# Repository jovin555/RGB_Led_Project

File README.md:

# ESP32 WS2812B LED Controller

A simple RGB LED chain controller for lighting up a Christmas tree with an ESP32. It is a 4-output, 5 V addressable LED controller built around the ESP32-S3-WROOM-1, designed to run [WLED](https://kno.wled.ge/). The repo holds the KiCad design, a 3D-printable enclosure, and the build and programming docs.

## Features

- **ESP32-S3-WROOM-1** (N8 or N8R8) with Wi-Fi, flashed over native USB-C. No USB-UART chip needed.
- **4 LED outputs** (GPIO4–7) through a 74AHCT125 3.3 V → 5 V level shifter, each on a 3-pin terminal (+5V / DATA / GND).
- **5 V input up to 10 A** through a screw terminal, plus a barrel jack (≤5 A), protected by a 7.5 A blade fuse and an SMBJ5.0A TVS diode.
- USB-C powers the logic for programming, isolated from the LED supply by ORing diodes and a 500 mA PTC.
- RST and BOOT buttons, a backup UART header (J3), and test points on every power rail.
- 110 × 85 mm, 2-layer board with 2 oz copper, laid out for JLCPCB assembly. ERC and DRC are clean (rev 0.2).

## Repository layout

| Path | Contents |
| --- | --- |
| [kicad/](kicad/) | KiCad project: schematic (root plus power, MCU, USB and LED-output sheets), PCB and project library |
| [enclosure/](enclosure/) | Parametric enclosure (CadQuery), printable STL/STEP parts, full assembly STEP and renders |
| [firmware/docs/](firmware/docs/) | Programming guide for WLED and Arduino/PlatformIO |
| [docs/](docs/) | Design plan, layout notes, enclosure design and images (each as Markdown and PDF) |
| [tools/kigen/](tools/kigen/) | Python scripts that generate the schematic sheets and PCB |

## Documentation

- [PCB design plan](docs/PCB_DESIGN_PLAN.md): why an ESP32, requirements, schematic blocks and BOM
- [Schematic and layout notes](docs/PCB_LAYOUT_NOTES.md): rev 0.2 status, changes, review fixes and the pre-order checklist
- [Enclosure design](docs/ENCLOSURE_DESIGN.md): how to view, print, order and assemble the enclosure
- [Programming guide](firmware/docs/PROGRAMMING_GUIDE.md): flashing WLED or your own code, pin map and troubleshooting

## Quick start

1. **Build the board:** open `kicad/esp32_led_controller.kicad_pro` in KiCad, then export Gerbers, BOM and positions for ordering. See [Check before ordering](docs/PCB_LAYOUT_NOTES.md#check-before-ordering).
2. **Print the enclosure:** print `enclosure/enclosure_base.stl`, `enclosure/enclosure_lid.stl` and two `enclosure/button_plunger.stl`. You'll also need four M3 screws and heat-set inserts ([parts list](docs/ENCLOSURE_DESIGN.md#parts-to-buy)).
3. **Flash WLED:** connect USB-C and use the WLED web installer ([guide](firmware/docs/PROGRAMMING_GUIDE.md#option-a-wled-recommended)). Set the LED outputs to GPIO 4, 5, 6 and 7.

## Regenerating

From the project root:

```bash
python3 -I tools/kigen/design.py     # rewrite the four schematic sub-sheets
# Do not run tools/kigen/pcbgen.py: it rebuilds the board and discards all routing.
python3 enclosure/enclosure.py       # rebuild the enclosure STL/STEP parts
python3 enclosure/make_assembly.py   # rebuild the assembly STEP files
```

Before you run these, read the Regenerating sections in [PCB_LAYOUT_NOTES.md](docs/PCB_LAYOUT_NOTES.md#regenerating) and [ENCLOSURE_DESIGN.md](docs/ENCLOSURE_DESIGN.md#regenerating) for the dependencies and caveats.

## Status

Rev 0.2: the design is complete and the board has not been fabricated yet.

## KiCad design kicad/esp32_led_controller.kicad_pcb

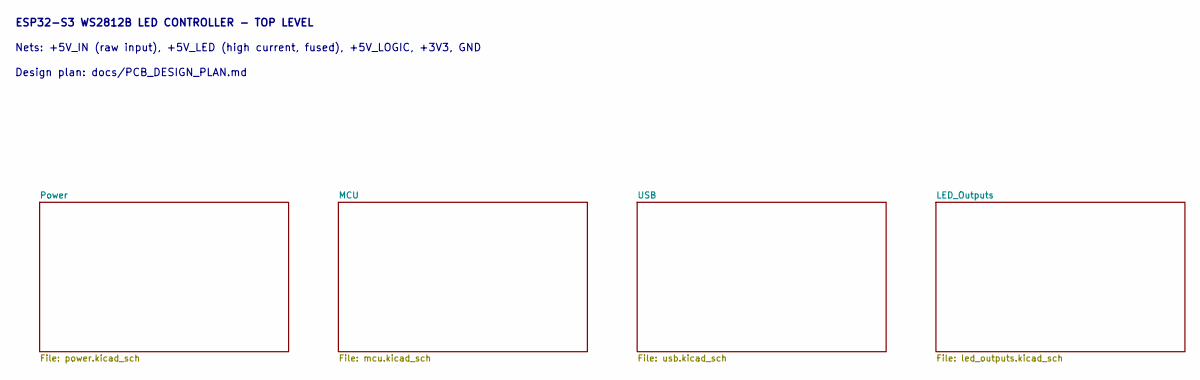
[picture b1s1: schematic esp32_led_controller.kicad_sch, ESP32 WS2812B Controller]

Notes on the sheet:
Design plan: docs/PCB_DESIGN_PLAN.md
ESP32-S3 WS2812B LED CONTROLLER - TOP LEVEL
Nets: +5V_IN (raw input), +5V_LED (high current, fused), +5V_LOGIC, +3V3, GND

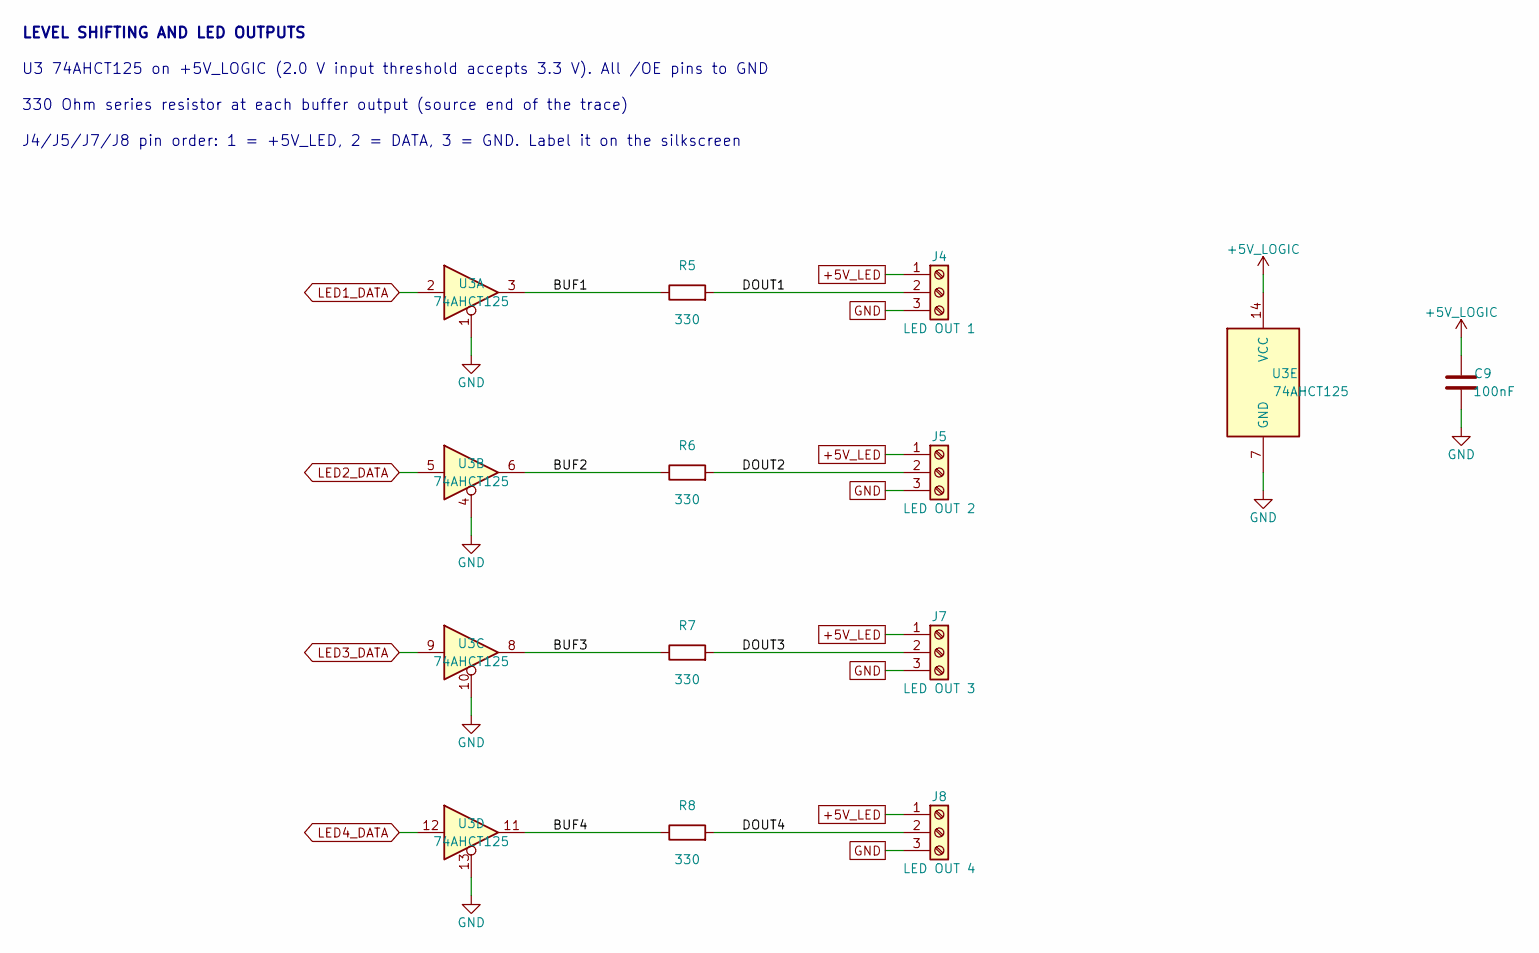
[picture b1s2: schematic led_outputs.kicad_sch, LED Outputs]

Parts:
C9: 100nF; C_0603_1608Metric
J4: LED OUT 1; TerminalBlock_Phoenix_MKDS-1,5-3-5.08_1x03_P5.08mm_Horizont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
J5: LED OUT 2; TerminalBlock_Phoenix_MKDS-1,5-3-5.08_1x03_P5.08mm_Horizont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
J7: LED OUT 3; TerminalBlock_Phoenix_MKDS-1,5-3-5.08_1x03_P5.08mm_Horizont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
J8: LED OUT 4; TerminalBlock_Phoenix_MKDS-1,5-3-5.08_1x03_P5.08mm_Horizont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
R5, R6, R7, R8: 330; R_0603_1608Metric
U3: 74AHCT125; SOIC-14_3.9x8.7mm_P1.27mm

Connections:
+5V_LED: J4.1, J5.1, J7.1, J8.1; also elsewhere on the board
+5V_LOGIC: C9.1, U3.14 (VCC); also elsewhere on the board
/LED_Outputs/BUF1: R5.1, U3.3
/LED_Outputs/BUF2: R6.1, U3.6
/LED_Outputs/BUF3: R7.1, U3.8
/LED_Outputs/BUF4: R8.1, U3.11
/LED_Outputs/DOUT1: J4.2, R5.2
/LED_Outputs/DOUT2: J5.2, R6.2
/LED_Outputs/DOUT3: J7.2, R7.2
/LED_Outputs/DOUT4: J8.2, R8.2
GND: C9.2, J4.3, J5.3, J7.3, J8.3, U3.1, U3.4, U3.7 (GND), U3.10, U3.13; also elsewhere on the board
LED1_DATA: U3.2; also elsewhere on the board
LED2_DATA: U3.5; also elsewhere on the board
LED3_DATA: U3.9; also elsewhere on the board
LED4_DATA: U3.12; also elsewhere on the board

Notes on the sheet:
LEVEL SHIFTING AND LED OUTPUTS
U3 74AHCT125 on +5V_LOGIC (2.0 V input threshold accepts 3.3 V). All /OE pins to GND
330 Ohm series resistor at each buffer output (source end of the trace)
J4/J5/J7/J8 pin order: 1 = +5V_LED, 2 = DATA, 3 = GND. Label it on the silkscreen

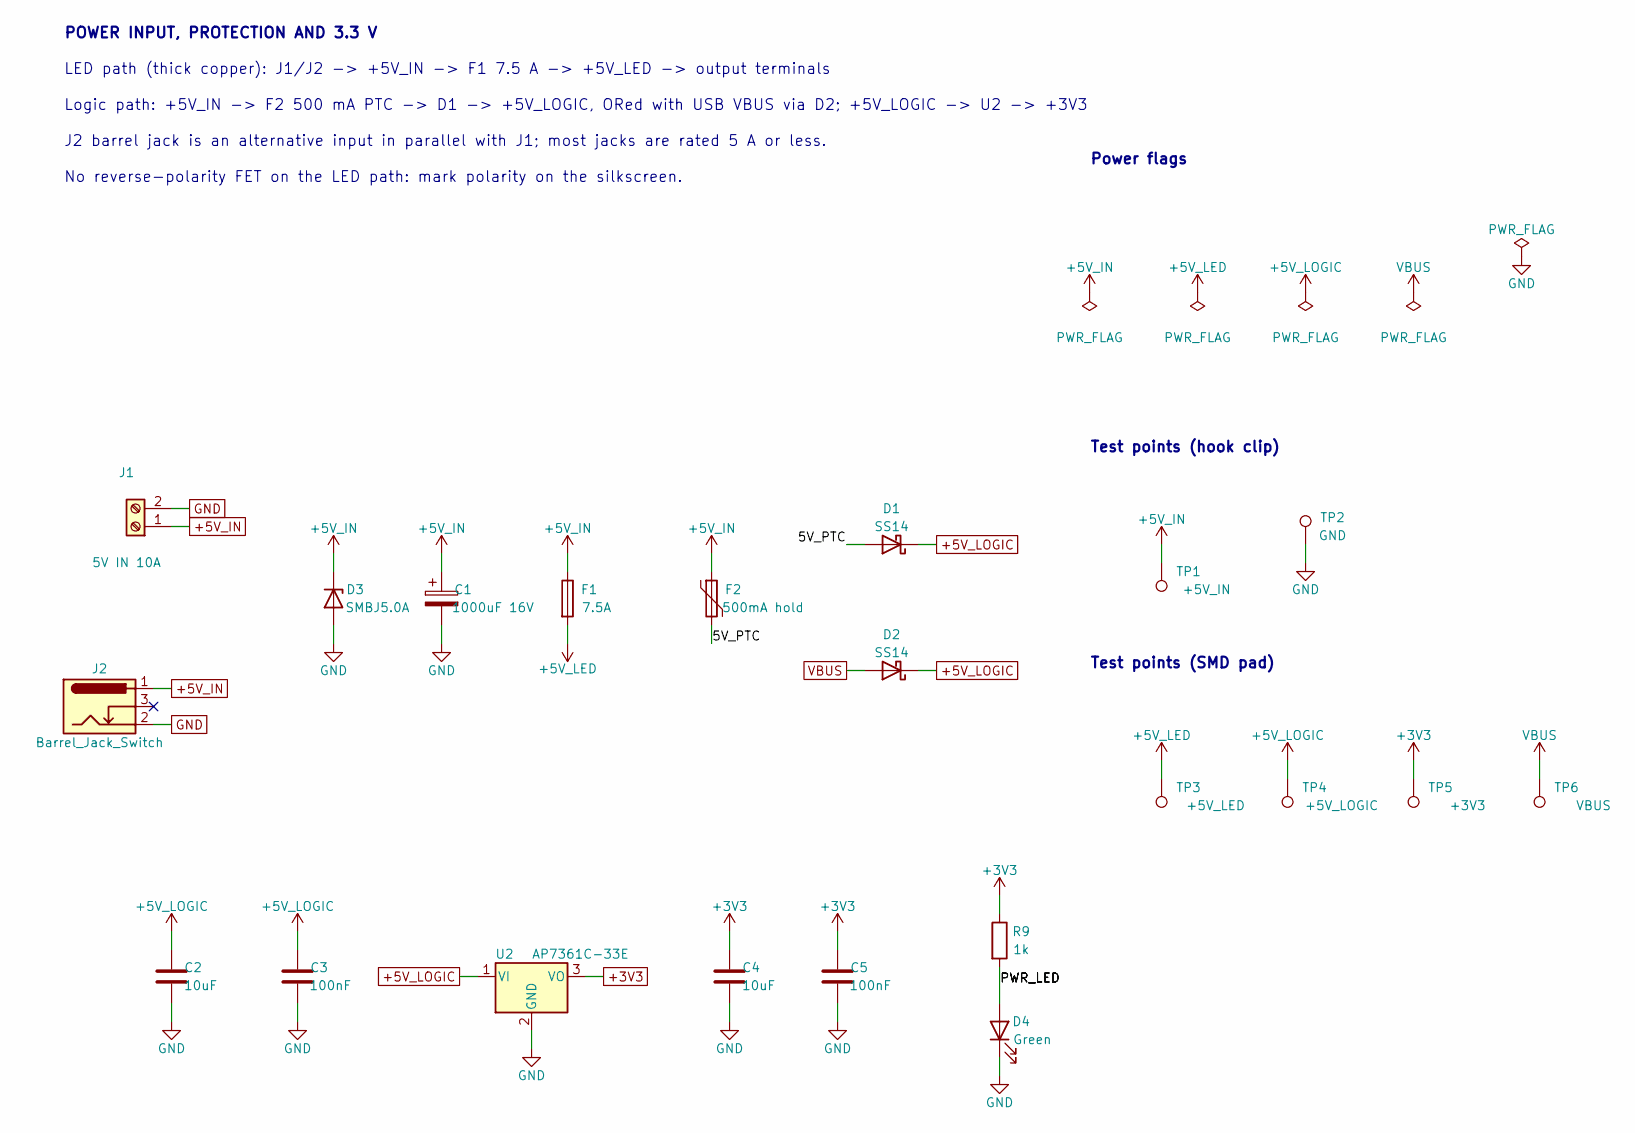
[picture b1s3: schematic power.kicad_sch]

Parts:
C1: 1000uF 16V; CP_Radial_D10.0mm_P5.00mm
C2, C4: 10uF; C_0805_2012Metric
C3, C5: 100nF; C_0603_1608Metric
D1, D2: SS14; D_SMA
D3: SMBJ5.0A; D_SMB
D4: Green; LED_0603_1608Metric
F1: 7.5A; Fuseholder_Blade_Mini_Keystone_3568
F2: 500mA hold; Fuse_1206_3216Metric
J1: 5V IN 10A; TerminalBlock_Phoenix_MKDS-1,5-2-5.08_1x02_P5.08mm_Horizont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
J2: Barrel_Jack_Switch; BarrelJack_Horizontal
R9: 1k; R_0603_1608Metric
TP1: +5V_IN; TestPoint_Keystone_5005-5009_Compact; MPN Keystone 5005 (red)
TP2: GND; TestPoint_Keystone_5005-5009_Compact; MPN Keystone 5006 (black)
TP3: +5V_LED; TestPoint_Pad_D1.5mm
TP4: +5V_LOGIC; TestPoint_Pad_D1.5mm
TP5: +3V3; TestPoint_Pad_D1.5mm
TP6: VBUS; TestPoint_Pad_D1.5mm
U2: AP7361C-33E; SOT-223-3_TabPin2

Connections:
+3V3: C4.1, C5.1, R9.1, TP5.1, U2.3 (VO); also elsewhere on the board
+5V_IN: C1.1, D3.1 (K), F1.1, F2.1, J1.1, J2.1, TP1.1
+5V_LED: F1.2, TP3.1; also elsewhere on the board
+5V_LOGIC: C2.1, C3.1, D1.1 (K), D2.1 (K), TP4.1, U2.1 (VI); also elsewhere on the board
/Power/5V_PTC: D1.2 (A), F2.2
/Power/PWR_LED: D4.2 (A), R9.2
GND: C1.2, C2.2, C3.2, C4.2, C5.2, D3.2 (A), D4.1 (K), J1.2, J2.2, TP2.1, U2.2 (GND); also elsewhere on the board
VBUS: D2.2 (A), TP6.1; also elsewhere on the board

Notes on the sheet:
POWER INPUT, PROTECTION AND 3.3 V
LED path (thick copper): J1/J2 -> +5V_IN -> F1 7.5 A -> +5V_LED -> output terminals
Logic path: +5V_IN -> F2 500 mA PTC -> D1 -> +5V_LOGIC, ORed with USB VBUS via D2; +5V_LOGIC -> U2 -> +3V3
J2 barrel jack is an alternative input in parallel with J1; most jacks are rated 5 A or less.
No reverse-polarity FET on the LED path: mark polarity on the silkscreen.
Test points (hook clip)
Test points (SMD pad)
Power flags

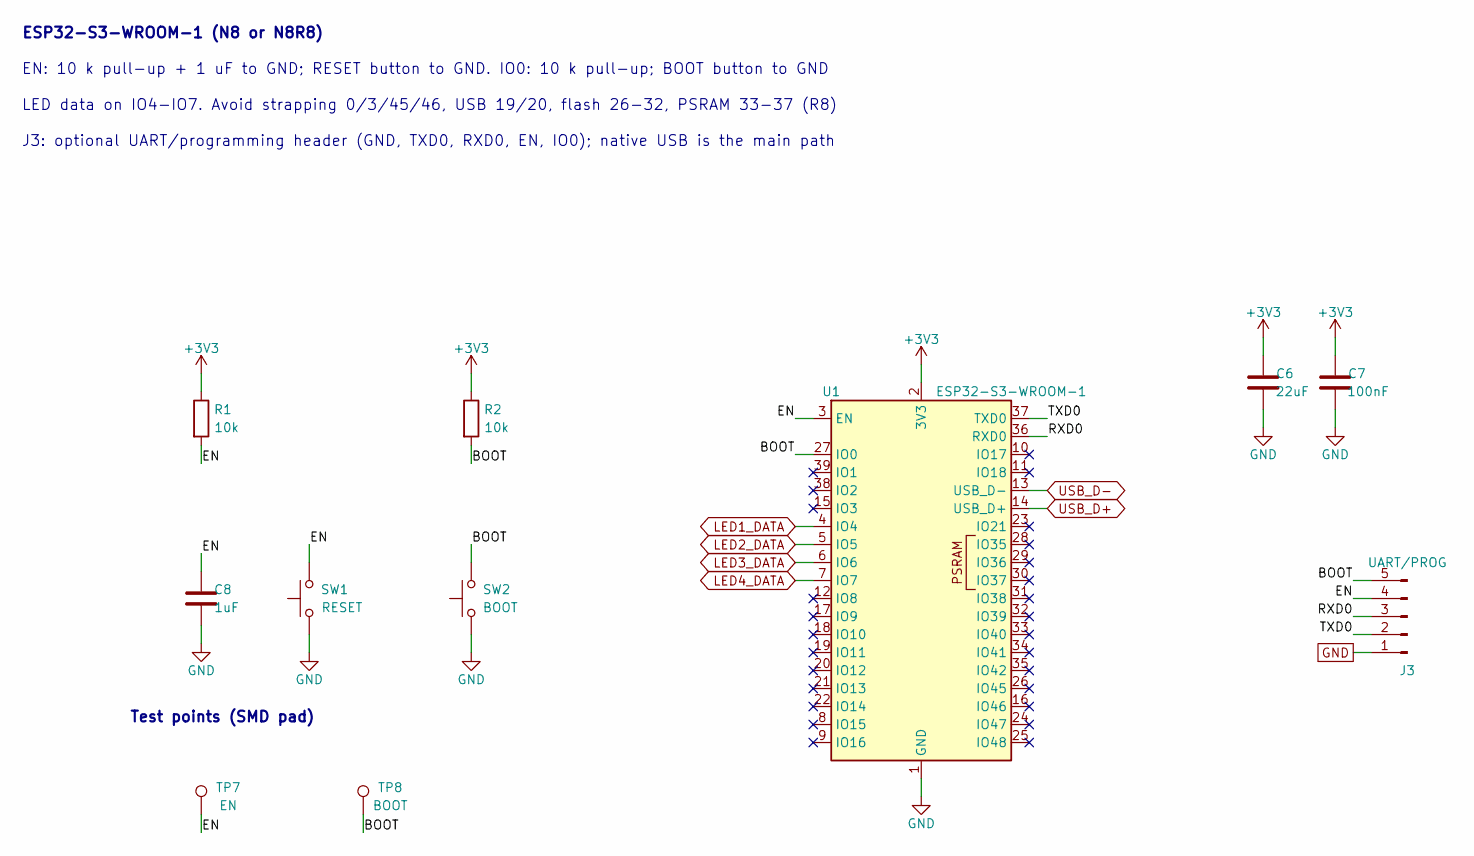
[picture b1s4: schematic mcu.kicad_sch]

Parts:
C6: 22uF; C_0805_2012Metric
C7: 100nF; C_0603_1608Metric
C8: 1uF; C_0603_1608Metric
J3: UART/PROG; PinHeader_1x05_P2.54mm_Vertical
R1, R2: 10k; R_0603_1608Metric
SW1: RESET; SW_SPST_TL3342
SW2: BOOT; SW_SPST_TL3342
TP7: EN; TestPoint_Pad_D1.5mm
TP8: BOOT; TestPoint_Pad_D1.5mm
U1: ESP32-S3-WROOM-1

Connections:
+3V3: C6.1, C7.1, R1.1, R2.1, U1.2 (3V3); also elsewhere on the board
/MCU/BOOT: J3.5, R2.2, SW2.2, TP8.1, U1.27 (IO0)
/MCU/EN: C8.1, J3.4, R1.2, SW1.2, TP7.1, U1.3 (EN)
/MCU/RXD0: J3.3, U1.36 (RXD0)
/MCU/TXD0: J3.2, U1.37 (TXD0)
GND: C6.2, C7.2, C8.2, J3.1, SW1.1, SW2.1, U1.1 (GND), U1.40 (GND), U1.41 (GND); also elsewhere on the board
LED1_DATA: U1.4 (IO4); also elsewhere on the board
LED2_DATA: U1.5 (IO5); also elsewhere on the board
LED3_DATA: U1.6 (IO6); also elsewhere on the board
LED4_DATA: U1.7 (IO7); also elsewhere on the board
USB_D+: U1.14 (USB_D+); also elsewhere on the board
USB_D-: U1.13 (USB_D-); also elsewhere on the board

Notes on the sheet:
ESP32-S3-WROOM-1 (N8 or N8R8)
EN: 10 k pull-up + 1 uF to GND; RESET button to GND. IO0: 10 k pull-up; BOOT button to GND
LED data on IO4-IO7. Avoid strapping 0/3/45/46, USB 19/20, flash 26-32, PSRAM 33-37 (R8)
J3: optional UART/programming header (GND, TXD0, RXD0, EN, IO0); native USB is the main path
Test points (SMD pad)

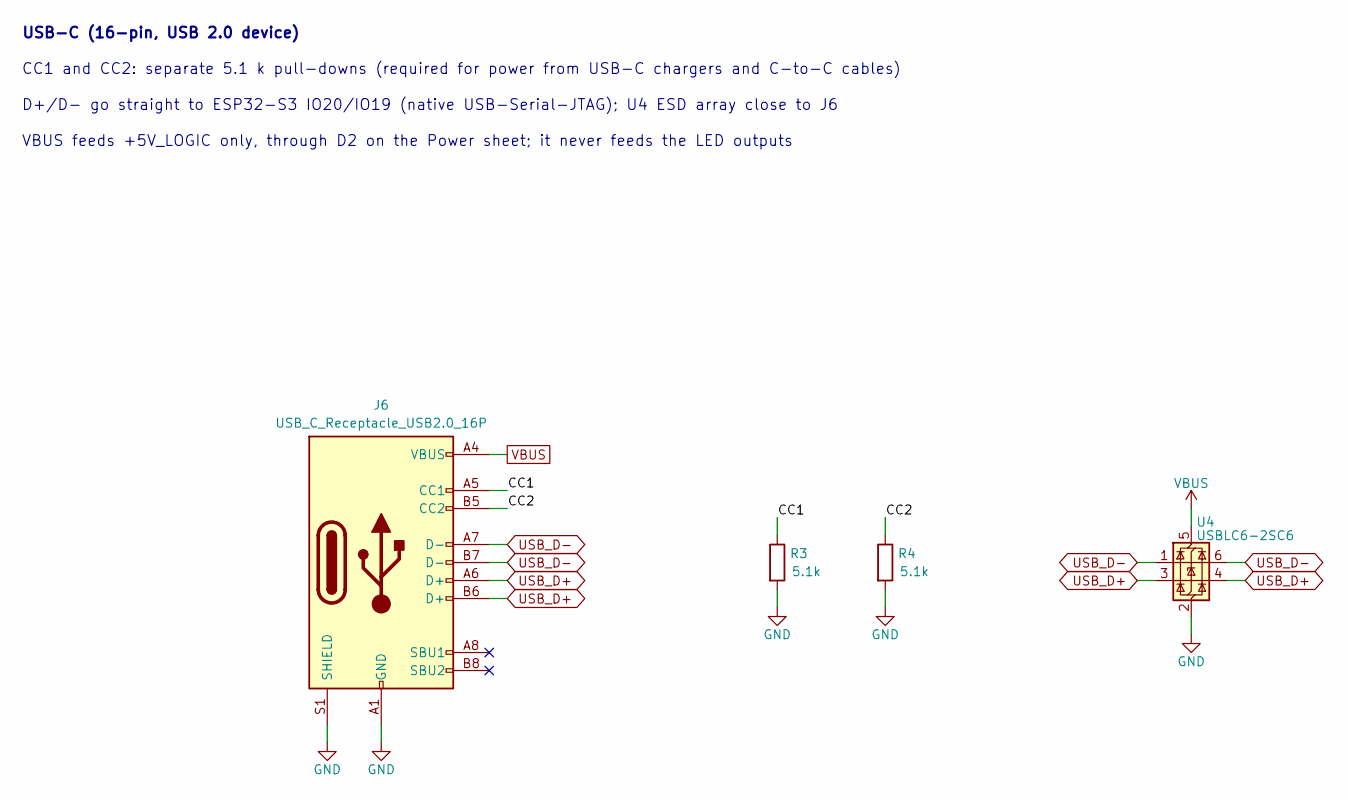
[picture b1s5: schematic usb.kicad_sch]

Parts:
J6: USB_C_Receptacle_USB2.0_16P; USB_C_Receptacle_HRO_TYPE-C-31-M-12
R3, R4: 5.1k; R_0603_1608Metric
U4: USBLC6-2SC6; SOT-23-6

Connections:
/USB/CC1: J6.A5 (CC1), R3.1
/USB/CC2: J6.B5 (CC2), R4.1
GND: J6.A1 (GND), J6.A12 (GND), J6.B1 (GND), J6.B12 (GND), J6.S1 (SHIELD), R3.2, R4.2, U4.2 (GND); also elsewhere on the board
USB_D+: J6.A6 (D+), J6.B6 (D+), U4.3 (I/O2), U4.4 (I/O2); also elsewhere on the board
USB_D-: J6.A7 (D-), J6.B7 (D-), U4.1 (I/O1), U4.6 (I/O1); also elsewhere on the board
VBUS: J6.A4 (VBUS), J6.A9 (VBUS), J6.B4 (VBUS), J6.B9 (VBUS), U4.5 (VBUS); also elsewhere on the board

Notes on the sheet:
USB-C (16-pin, USB 2.0 device)
CC1 and CC2: separate 5.1 k pull-downs (required for power from USB-C chargers and C-to-C cables)
D+/D- go straight to ESP32-S3 IO20/IO19 (native USB-Serial-JTAG); U4 ESD array close to J6
VBUS feeds +5V_LOGIC only, through D2 on the Power sheet; it never feeds the LED outputs

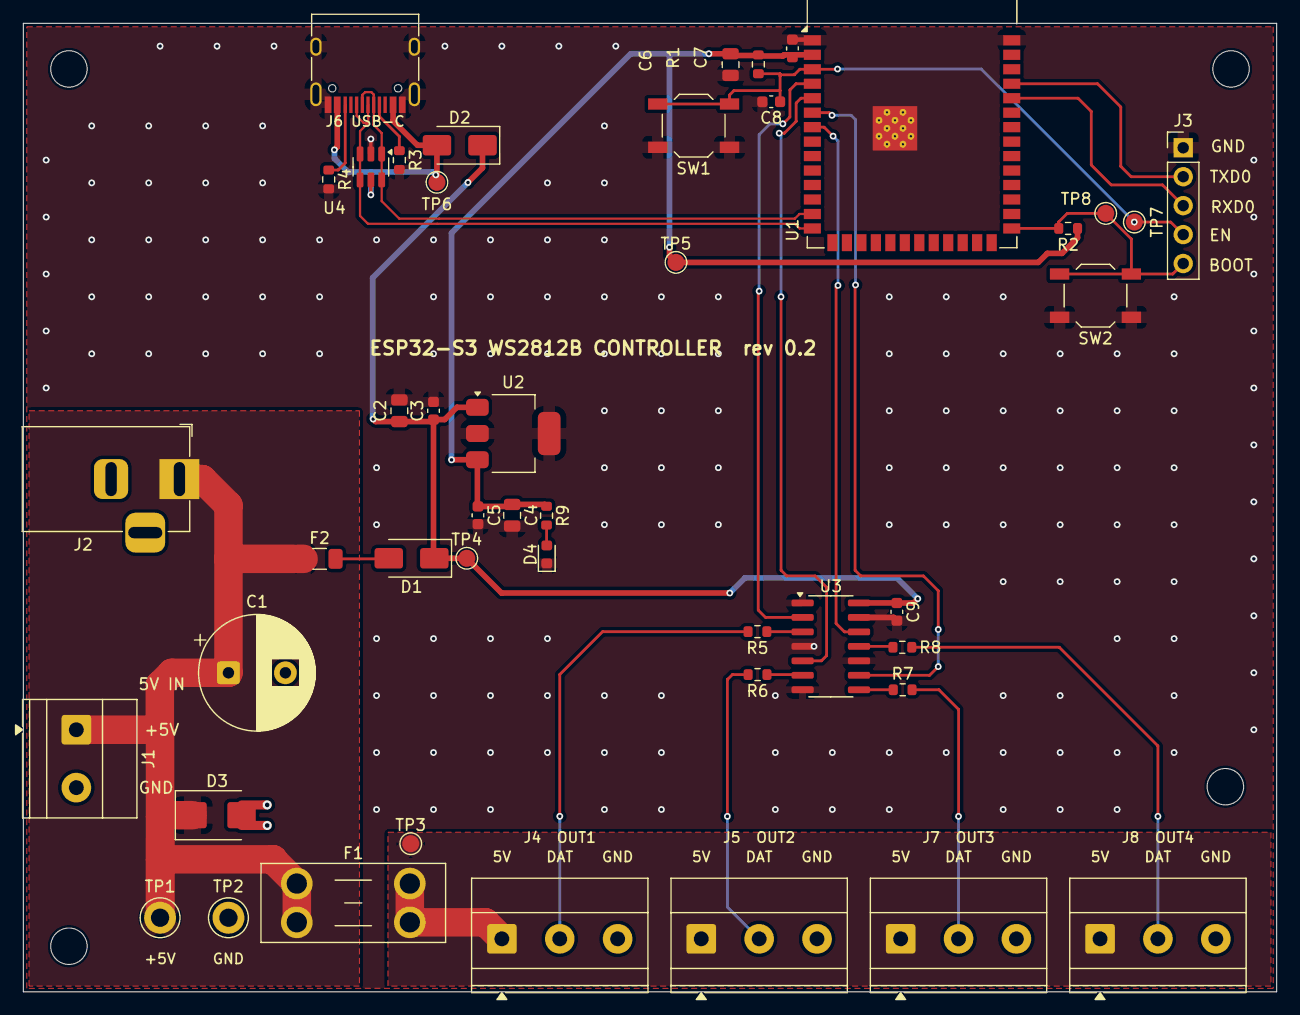
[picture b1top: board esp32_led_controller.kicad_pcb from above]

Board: 2 copper layers, 110.0 x 85.0 mm, 50 parts (0 on the bottom side), 28 nets.

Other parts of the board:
H1, H2, H3, H4: M3; MountingHole_3.2mm_M3

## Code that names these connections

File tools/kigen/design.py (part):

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        "LED data on IO4-IO7. Avoid strapping 0/3/45/46, USB 19/20, flash 26-32, PSRAM 33-37 (R8)",
        "J3: optional UART/programming header (GND, TXD0, RXD0, EN, IO0); native USB is the main path",
    ])
    gpio = {"3": "/EN", "27": "/BOOT", "4": "LED1_DATA", "5": "LED2_DATA", "6": "LED3_DATA",
            "7": "LED4_DATA", "13": "USB_D-", "14": "USB_D+", "37": "/TXD0", "36": "/RXD0",
            "2": "+3V3", "1": "GND"}
    s.part("RF_Module:ESP32-S3-WROOM-1", "U1", "ESP32-S3-WROOM-1", "RF_Module:ESP32-S3-WROOM-1",
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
